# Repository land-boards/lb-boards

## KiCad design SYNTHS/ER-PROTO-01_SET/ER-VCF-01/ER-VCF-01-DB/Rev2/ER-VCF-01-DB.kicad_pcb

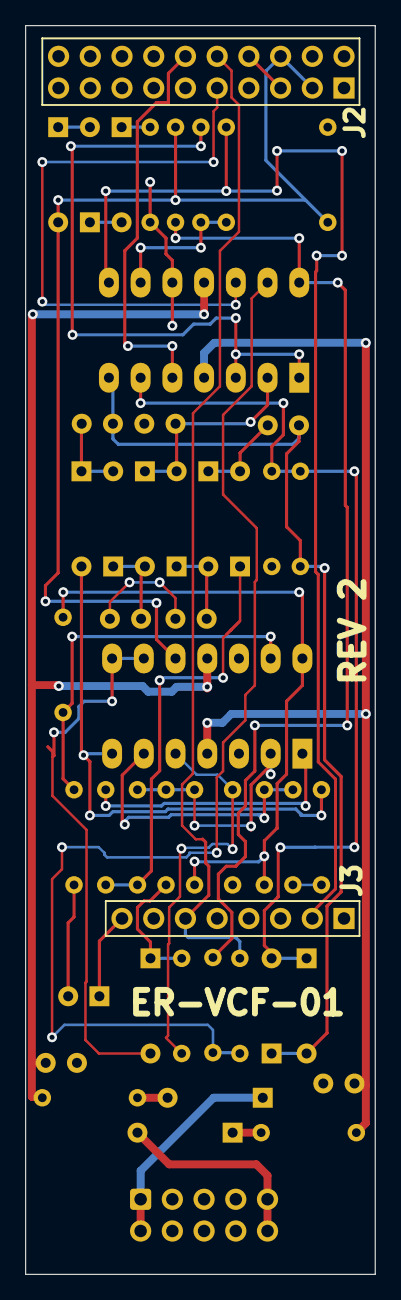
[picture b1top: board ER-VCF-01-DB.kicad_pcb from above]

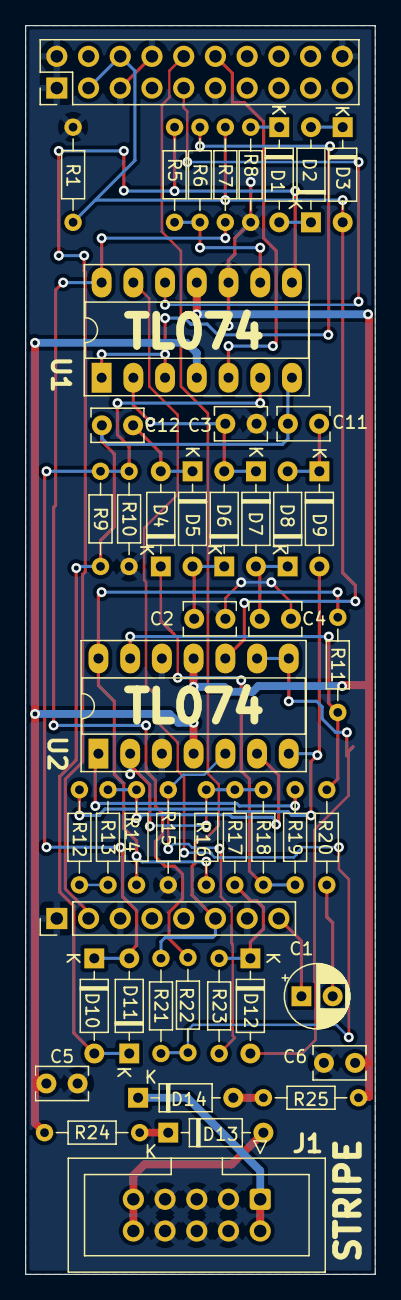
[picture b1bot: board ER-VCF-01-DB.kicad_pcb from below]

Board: 2 copper layers, 28.0 x 100.0 mm, 49 parts (49 on the bottom side), 39 nets.

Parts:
C1: 1uF; CP_Radial_D5.0mm_P2.50mm
C2, C3, C4, C11, C12: 1nF; C_Rect_L4.0mm_W2.5mm_P2.50mm
C5, C6: 0.1uF; C_Rect_L4.0mm_W2.5mm_P2.50mm
D1, D2, D3, D4, D5, D6, D7, D8, D9, D10, D11, D12, D13, D14: 1N4148; D_DO-35_SOD27_P7.62mm_Horizontal
J1: ER-PWR-2X5; IDC-Header_2x05_P2.54mm_Vertical
J2: PROTO01_POTS; PinHeader_2x10_P2.54mm_Vertical
J3: PROTO01_JACKS; PinHeader_1x08_P2.54mm_Vertical
R1, R9: 10K; R_Axial_DIN0204_L3.6mm_D1.6mm_P7.62mm_Horizontal
R5: 47K; R_Axial_DIN0204_L3.6mm_D1.6mm_P7.62mm_Horizontal
R6, R8, R11: 1K; R_Axial_DIN0204_L3.6mm_D1.6mm_P7.62mm_Horizontal
R7, R20, R21, R22: 100K; R_Axial_DIN0204_L3.6mm_D1.6mm_P7.62mm_Horizontal
R10, R12, R19: 2.2K; R_Axial_DIN0204_L3.6mm_D1.6mm_P7.62mm_Horizontal
R13, R14, R15, R16, R17, R18, R23: 33K; R_Axial_DIN0204_L3.6mm_D1.6mm_P7.62mm_Horizontal
R24, R25: 10; R_Axial_DIN0204_L3.6mm_D1.6mm_P7.62mm_Horizontal
U1, U2: TL074; DIP-14_W7.62mm_Socket_LongPads

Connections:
+12V: C5.1, R24.2, U1.4 (V+), U2.4 (V+)
-12V: C6.2, R25.2, U1.11 (V-), U2.11 (V-)
/AUDIO: R11.2, R14.1, R16.1, U2.14
/CV: D12.1 (K), R17.1, R23.1
/J1-T: C1.1, J3.8 (J1-T)
/J3-T: J2.10 (POT2_3_CCW), J3.6 (J3-T), R21.1
/J4-T: J3.2 (J4-T), R5.2, U1.8
/POT2-2: J2.9 (POT2_2_W), U1.12 (+)
/POT4-2: D3.2 (A), J2.3 (POT6_2_W), J2.6 (POT4_2_W), R1.2, R7.2, U2.10 (+)
/POT5-2: J2.12 (POT5_2_W), U1.5 (+)
GND: C2.2, C3.2, C4.2, C5.2, C6.1, J1.3 (GND), J1.4 (GND), J1.5 (GND), J1.6 (GND), J1.7 (GND), J1.8 (GND), J2.1 (GND), J2.2 (POT6_1_CW), J2.5 (POT4_1_CW), J2.8 (POT2_1_CW), J2.11 (POT5_1_CW), J2.20 (GND), J3.1 (J4-S), J3.3 (J2-S), J3.5 (J3-S), J3.7 (J1-S), R1.1, R8.1, R10.1, R15.1, U1.10 (+), U2.3 (+), U2.12 (+)
unnamed: C1.2, R20.1
unnamed: C2.1, D7.2 (A), D8.1 (K)
unnamed: C3.1, D6.2 (A), D7.1 (K), U1.2 (-)
unnamed: C4.1, D5.2 (A), D6.1 (K)
unnamed: C11.1, C12.1, D10.2 (A), D11.1 (K), R9.1, U1.7
unnamed: C11.2, D8.2 (A), D9.1 (K)
unnamed: C12.2, D4.2 (A), D5.1 (K)
unnamed: D1.1 (K), R8.2
unnamed: D1.2 (A), D2.1 (K)
unnamed: D2.2 (A), D3.1 (K)
unnamed: D4.1 (K), R18.2, R19.2
unnamed: D9.2 (A), R12.1, U2.7
unnamed: D10.1 (K), D11.2 (A), R9.2, R10.2, U1.6 (-)
unnamed: D12.2 (A), U2.8, U2.9 (-)
unnamed: D13.1 (K), R24.1
unnamed: D13.2 (A), J1.9 (+12V), J1.10 (+12V)
unnamed: D14.1 (K), J1.1 (-12V), J1.2 (-12V)
unnamed: D14.2 (A), R25.1
unnamed: R5.1, R6.1, U1.9 (-)
unnamed: R6.2, U1.1, U1.3 (+)
unnamed: R11.1, R20.2, U2.13 (-)
unnamed: R12.2, R13.2
unnamed: R13.1, R14.2, U2.6 (-)
unnamed: R15.2, R23.2, U2.5 (+)
unnamed: R16.2, R17.2, R18.1, U2.2 (-)
unnamed: R19.1, U2.1
unnamed: R21.2, R22.1, U1.13 (-)
unnamed: R7.1, R22.2, U1.14

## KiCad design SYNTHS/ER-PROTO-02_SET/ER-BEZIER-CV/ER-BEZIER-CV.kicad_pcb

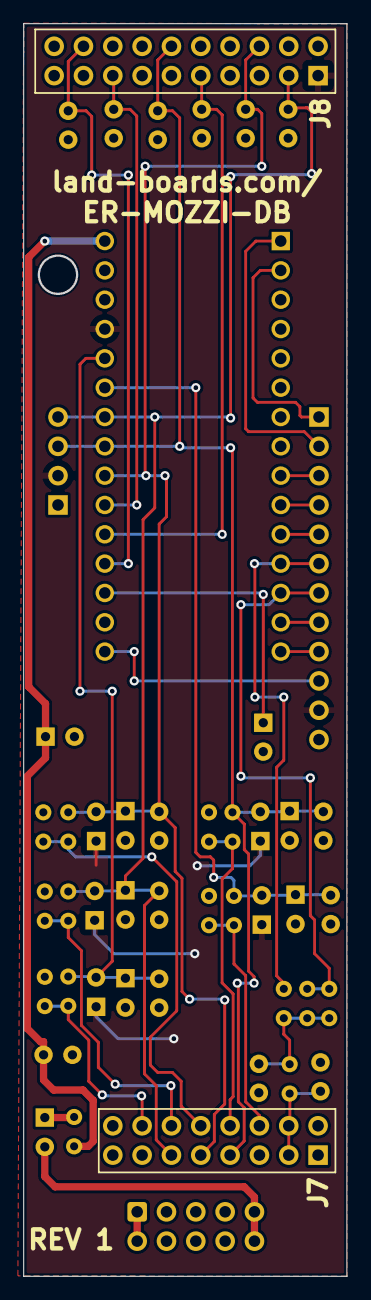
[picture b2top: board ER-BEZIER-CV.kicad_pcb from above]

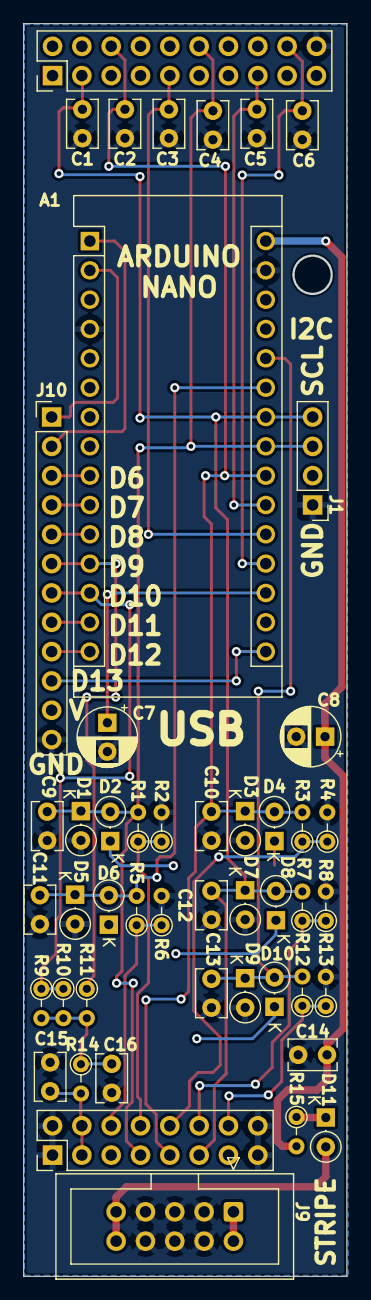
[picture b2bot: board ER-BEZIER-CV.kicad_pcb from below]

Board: 2 copper layers, 28.0 x 108.5 mm, 48 parts (48 on the bottom side), 32 nets.

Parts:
A1: Arduino_Nano_v3.x; Arduino_Nano
C1, C2, C3, C4, C5, C6, C9, C10, C11, C12, C13, C14: 0.1uF; C_Rect_L4.0mm_W2.5mm_P2.50mm
C7: 10uF; CP_Radial_D5.0mm_P2.50mm
C8: 47uF; CP_Radial_D5.0mm_P2.50mm
C15: 10nF; C_Rect_L4.0mm_W2.5mm_P2.50mm
C16: 4.7nF; C_Rect_L4.0mm_W2.5mm_P2.50mm
D1, D2, D3, D4, D5, D6, D7, D8, D9, D10, D11: BAT41; D_DO-35_SOD27_P2.54mm_Vertical_KathodeUp
J1: Conn_01x04; PinHeader_1x04_P2.54mm_Vertical
J7: PROTO02_JACKS; PinHeader_2x08_P2.54mm_Vertical
J8: PROTO01_POTS; PinHeader_2x10_P2.54mm_Vertical
J9: CONN, IDC, 2X5; IDC-Header_2x05_P2.54mm_Vertical
J10: Conn_01x12; PinHeader_1x12_P2.54mm_Vertical
R1, R3, R5, R7, R12: 10K; R_Axial_DIN0204_L3.6mm_D1.6mm_P2.54mm_Vertical
R2, R4, R6, R8, R13: 100K; R_Axial_DIN0204_L3.6mm_D1.6mm_P2.54mm_Vertical
R9, R10: 1M; R_Axial_DIN0204_L3.6mm_D1.6mm_P2.54mm_Vertical
R11, R14: 3.9K; R_Axial_DIN0204_L3.6mm_D1.6mm_P2.54mm_Vertical
R15: 10; R_Axial_DIN0204_L3.6mm_D1.6mm_P2.54mm_Vertical

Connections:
+5V: A1.27 (+5V), D2.1 (K), D4.1 (K), D6.1 (K), D8.1 (K), D10.1 (K), J1.2, J8.1 (GND), J10.11
+12P: A1.30 (VIN), C8.1, C14.1, R15.2
+12V: D11.2 (A), J9.9, J9.10
-12V: J9.1, J9.2
/D0_RX: A1.2 (D0/RX), J10.1
/D1_TX: A1.1 (D1/TX), J10.2
/D6: A1.9 (D6), J10.3
/D7: A1.10 (D7), J10.4
/D8: A1.11 (D8), J10.5
/D9: A1.12 (D9), J10.6, R11.1
/D10: A1.13 (D10), J10.7, R9.1, R10.1
/D11: A1.14 (D11), J10.8
/D12: A1.15 (D12), J10.9
/D13: A1.16 (D13), J10.10
/J1-R_N: A1.22 (A3), C2.1, C10.1, D3.1 (K), D4.2 (A), J7.9 (J1_R_N), J8.6 (POT4_2_W), R3.2
/J1-T: J7.10 (J1_T), R3.1, R4.1
/J2-R_N: A1.23 (A4), C4.1, C9.1, D1.1 (K), D2.2 (A), J1.3, J7.7 (J2_R_N), J8.12 (POT5_2_W), R1.2
/J2-T: J7.8 (J2_T), R1.1, R2.1
/J3-R_N: A1.24 (A5), C1.1, C12.1, D7.1 (K), D8.2 (A), J1.4, J7.11 (J3_R_N), J8.3 (POT6_2_W), R7.2
/J3-T: J7.12 (J3_T), R7.1, R8.1
/J4-T: J7.6 (J4_T), R5.1, R6.1
/J5-T: J7.14 (J5_T), R12.1, R13.1
/J6-R_N: C15.1, J7.3 (J6_R_N), J7.4 (J6_T), R14.2
/POT1-2: A1.19 (A0), C6.1, J8.18 (POT1_2_W)
/POT2-2: A1.20 (A1), C3.1, J8.9 (POT2_2_W)
/POT3-2: A1.21 (A2), C5.1, J8.15 (POT3_2_W)
GND: A1.4 (GND), A1.29 (GND), C1.2, C2.2, C3.2, C4.2, C5.2, C6.2, C7.2, C8.2, C9.2, C10.2, C11.2, C12.2, C13.2, C14.2, C15.2, C16.2, D1.2 (A), D3.2 (A), D5.2 (A), D7.2 (A), D9.2 (A), J1.1, J7.1 (GND), J7.2 (GND), J7.15 (GND), J7.16 (GND), J8.20 (GND), J9.3, J9.4, J9.5, J9.6, J9.7, J9.8, J10.12, R2.2, R4.2, R6.2, R8.2, R13.2
unnamed: A1.18 (AREF), C7.1
unnamed: A1.25 (A6), C11.1, D5.1 (K), D6.2 (A), R5.2
unnamed: A1.26 (A7), C13.1, D9.1 (K), D10.2 (A), R12.2
unnamed: C16.1, R9.2, R10.2, R11.2, R14.1
unnamed: D11.1 (K), R15.1

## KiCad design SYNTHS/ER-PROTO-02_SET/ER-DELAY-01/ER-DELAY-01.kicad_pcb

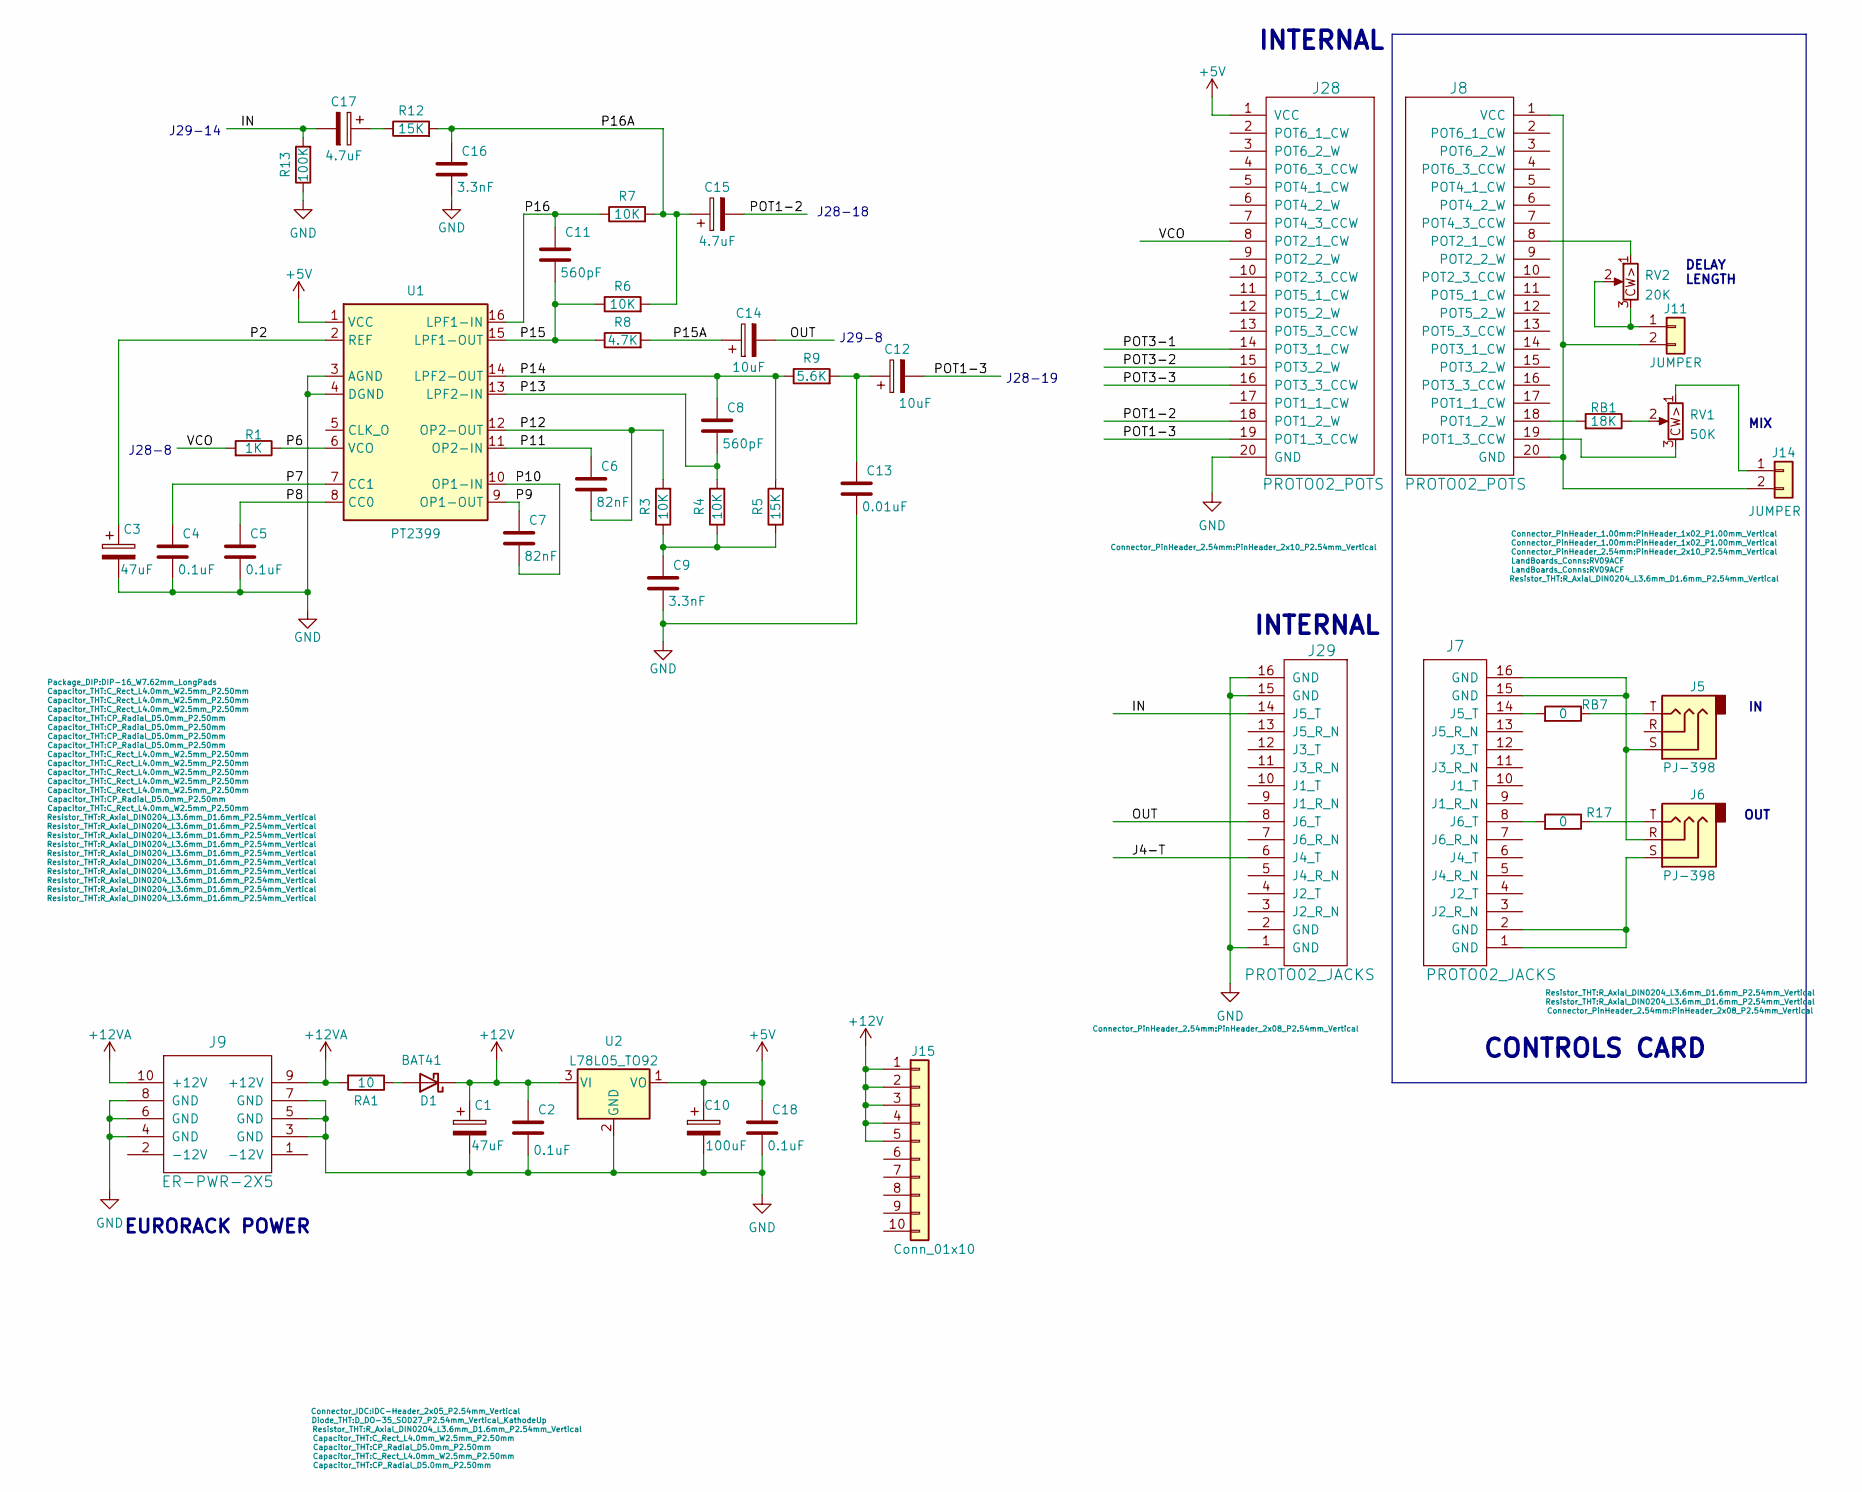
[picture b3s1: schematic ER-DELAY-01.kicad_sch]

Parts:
C1, C3: 47uF; CP_Radial_D5.0mm_P2.50mm
C2, C4, C5, C18: 0.1uF; C_Rect_L4.0mm_W2.5mm_P2.50mm
C6, C7: 82nF; C_Rect_L4.0mm_W2.5mm_P2.50mm
C8, C11: 560pF; C_Rect_L4.0mm_W2.5mm_P2.50mm
C9, C16: 3.3nF; C_Rect_L4.0mm_W2.5mm_P2.50mm
C10: 100uF; CP_Radial_D5.0mm_P2.50mm
C12, C14: 10uF; CP_Radial_D5.0mm_P2.50mm
C13: 0.01uF; C_Rect_L4.0mm_W2.5mm_P2.50mm
C15, C17: 4.7uF; CP_Radial_D5.0mm_P2.50mm
D1: BAT41; D_DO-35_SOD27_P2.54mm_Vertical_KathodeUp
J5, J6: PJ-398; Jack_3.5mm_QingPu_WQP-PJ366ST_Vertical
J7, J29: PROTO02_JACKS; PinHeader_2x08_P2.54mm_Vertical
J8, J28: PROTO02_POTS; PinHeader_2x10_P2.54mm_Vertical
J9: ER-PWR-2X5; IDC-Header_2x05_P2.54mm_Vertical
J11, J14: JUMPER; PinHeader_1x02_P1.00mm_Vertical
J15: Conn_01x10; PinHeader_1x10_P2.54mm_Vertical
R1: 1K; R_Axial_DIN0204_L3.6mm_D1.6mm_P2.54mm_Vertical
R3, R4, R6, R7: 10K; R_Axial_DIN0204_L3.6mm_D1.6mm_P2.54mm_Vertical
R5, R12: 15K; R_Axial_DIN0204_L3.6mm_D1.6mm_P2.54mm_Vertical
R8: 4.7K; R_Axial_DIN0204_L3.6mm_D1.6mm_P2.54mm_Vertical
R9: 5.6K; R_Axial_DIN0204_L3.6mm_D1.6mm_P2.54mm_Vertical
R13: 100K; R_Axial_DIN0204_L3.6mm_D1.6mm_P2.54mm_Vertical
R17: 0; R_Axial_DIN0204_L3.6mm_D1.6mm_P2.54mm_Vertical
RA1: 10; R_Axial_DIN0204_L3.6mm_D1.6mm_P2.54mm_Vertical
RB1: 18K; R_Axial_DIN0204_L3.6mm_D1.6mm_P2.54mm_Vertical
RB7: 0; R_Axial_DIN0204_L3.6mm_D1.6mm_P2.54mm_Vertical
RV1: 50K; RV09ACF
RV2: 20K; RV09ACF
U1: PT2399; DIP-16_W7.62mm_LongPads
U2: L78L05_TO92; TO-92_Inline

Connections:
+5V: C10.1, C18.1, J28.1 (VCC), U1.1 (VCC), U2.1 (VO)
+12V: C1.1, C2.1, D1.1 (K), J15.1, J15.2, J15.3, J15.4, J15.5, U2.3 (VI)
+12VA: J9.9 (+12V), J9.10 (+12V), RA1.2
/IN: C17.2, J29.14 (J5_T), R13.2
/J4-T: J29.6 (J4_T)
/OUT: C14.2, J29.8 (J6_T)
/POT1-2: C15.2, J28.18 (POT1_2_W)
/POT1-3: C12.2, J28.19 (POT1_3_CCW)
/POT3-1: J28.14 (POT3_1_CW)
/POT3-2: J28.15 (POT3_2_W)
/POT3-3: J28.16 (POT3_3_CCW)
/VCO: J28.8 (POT2_1_CW), R1.2
GND: C1.2, C2.2, C3.2, C4.2, C5.2, C9.2, C10.2, C13.2, C16.2, C18.2, J9.3 (GND), J9.4 (GND), J9.5 (GND), J9.6 (GND), J9.7 (GND), J9.8 (GND), J28.20 (GND), J29.1 (GND), J29.15 (GND), J29.16 (GND), R13.1, U1.3 (AGND), U1.4 (DGND), U2.2 (GND)
unnamed: C3.1, U1.2 (REF)
unnamed: C4.1, U1.7 (CC1)
unnamed: C5.1, U1.8 (CC0)
unnamed: C6.1, U1.11 (OP2-IN)
unnamed: C6.2, R3.2, U1.12 (OP2-OUT)
unnamed: C7.1, U1.9 (OP1-OUT)
unnamed: C7.2, U1.10 (OP1-IN)
unnamed: C8.1, R5.2, R9.1, U1.14 (LPF2-OUT)
unnamed: C8.2, R4.2, U1.13 (LPF2-IN)
unnamed: C9.1, R3.1, R4.1, R5.1
unnamed: C11.1, R7.1, U1.16 (LPF1-IN)
unnamed: C11.2, R6.1, R8.1, U1.15 (LPF1-OUT)
unnamed: C12.1, C13.1, R9.2
unnamed: C14.1, R8.2
unnamed: C15.1, C16.1, R6.2, R7.2, R12.2
unnamed: C17.1, R12.1
unnamed: D1.2 (A), RA1.1
unnamed: J5.S, J6.R, J7.15 (GND), J7.16 (GND)
unnamed: J5.T, RB7.1
unnamed: J6.S, J7.1 (GND), J7.2 (GND)
unnamed: J6.T, R17.1
unnamed: J7.8 (J6_T), R17.2
unnamed: J7.14 (J5_T), RB7.2
unnamed: J8.8 (POT2_1_CW), RV2.1
unnamed: J8.18 (POT1_2_W), RB1.2
unnamed: J8.19 (POT1_3_CCW), RV1.3
unnamed: J11.1, RV2.2, RV2.3
unnamed: J8.1 (VCC), J8.20 (GND), J11.2, J14.2
unnamed: J14.1, RV1.1
unnamed: R1.1, U1.6 (VCO)
unnamed: RB1.1, RV1.2

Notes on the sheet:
EURORACK POWER
INTERNAL
CONTROLS CARD
J29-14
MIX
J29-8
J28-18
J28-8
DELAY LENGTH
J28-19
OUT

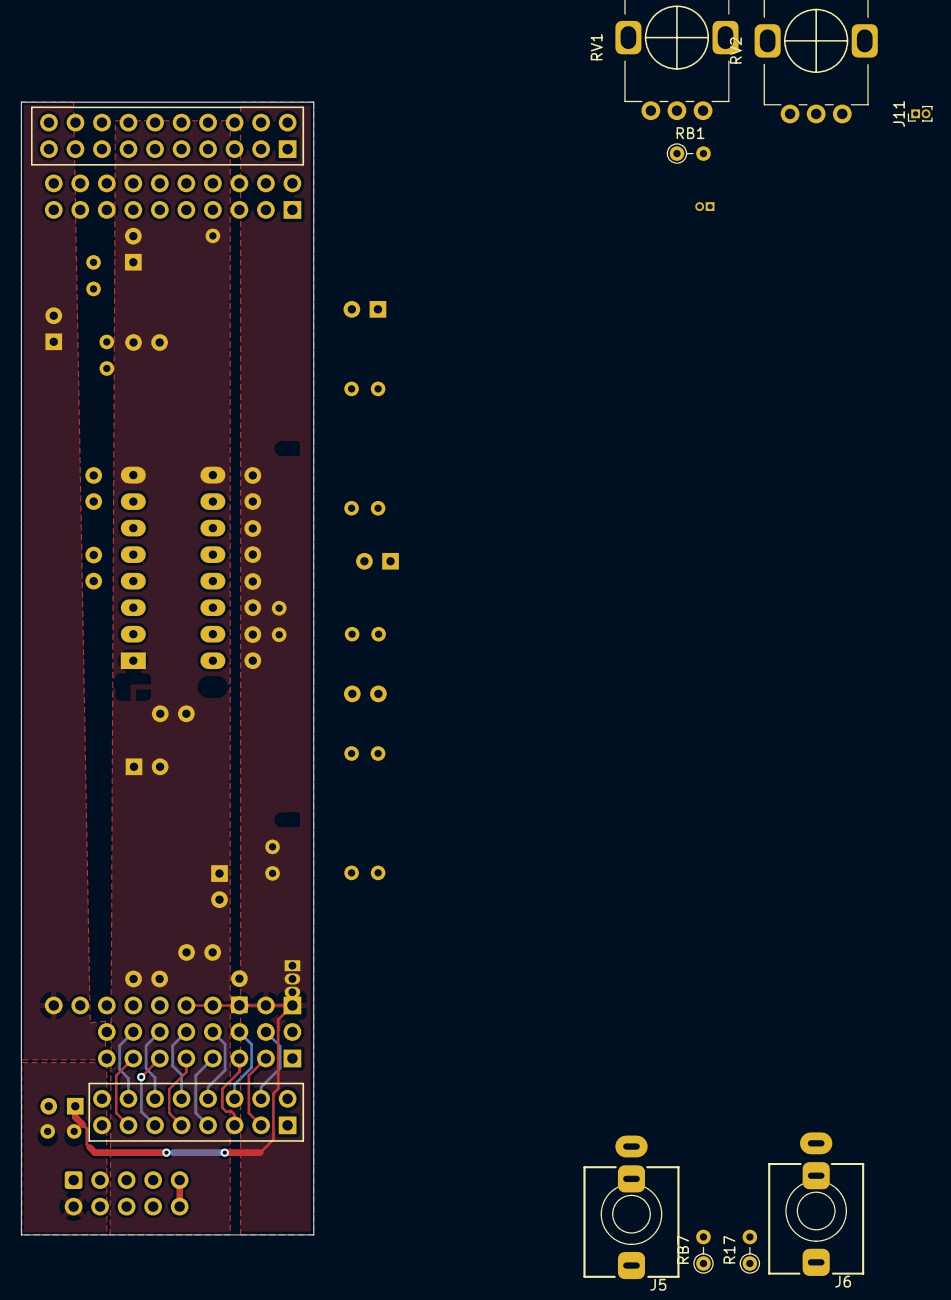
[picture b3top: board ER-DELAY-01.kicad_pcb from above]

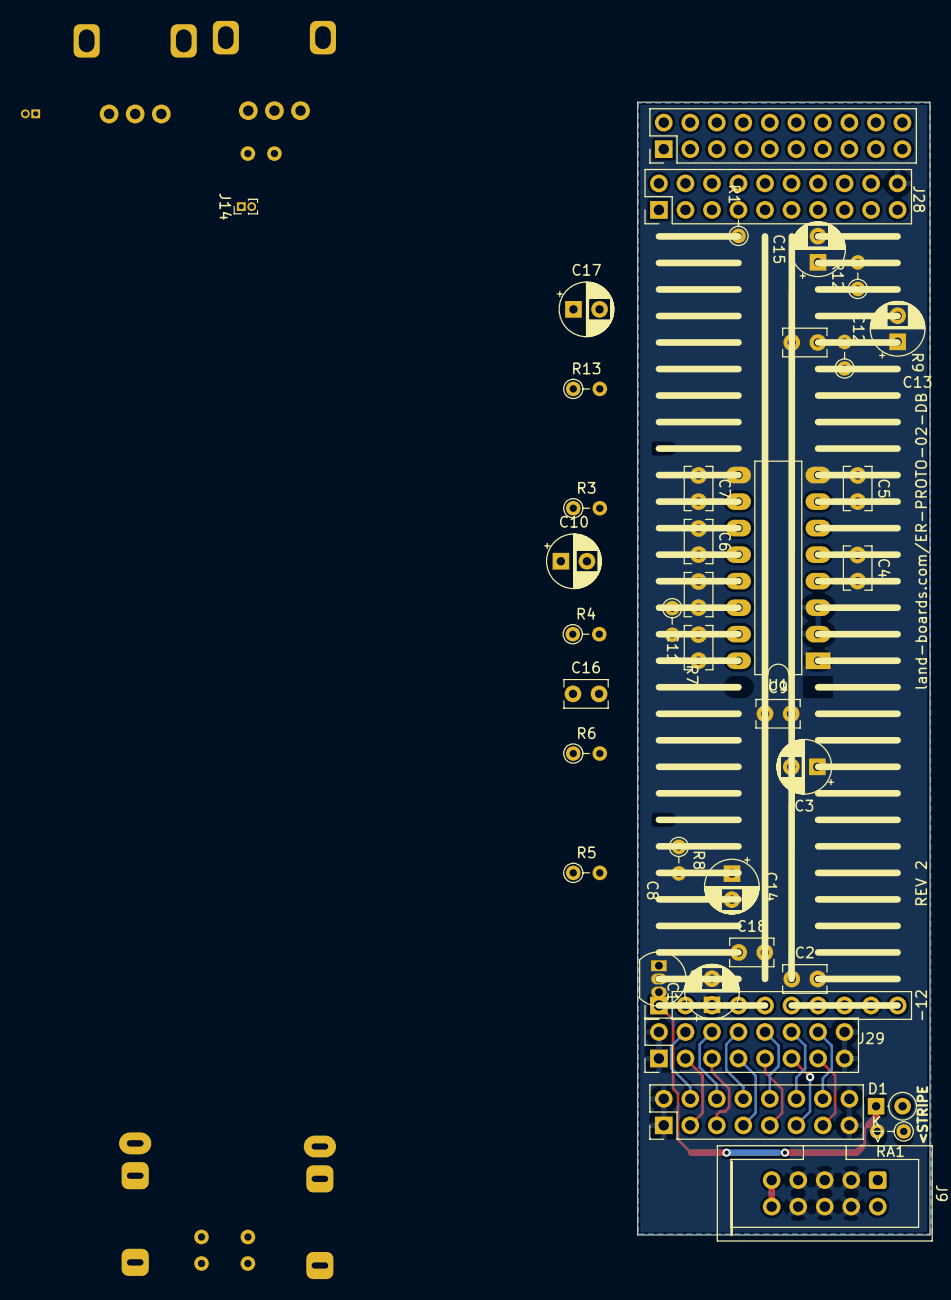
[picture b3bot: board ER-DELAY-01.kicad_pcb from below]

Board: 2 copper layers, 28.0 x 108.5 mm, 47 parts (39 on the bottom side), 40 nets.

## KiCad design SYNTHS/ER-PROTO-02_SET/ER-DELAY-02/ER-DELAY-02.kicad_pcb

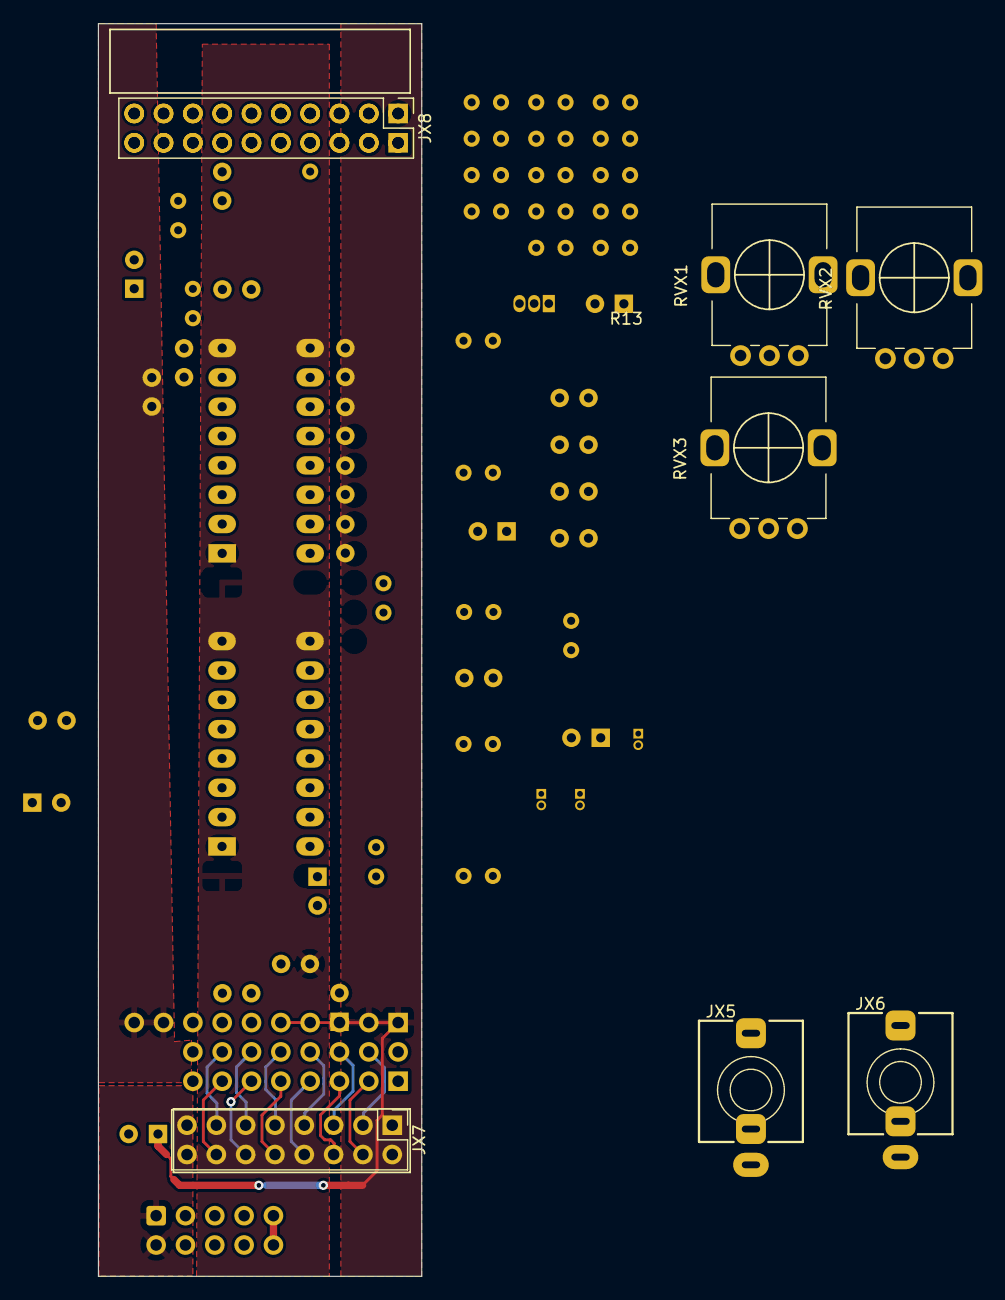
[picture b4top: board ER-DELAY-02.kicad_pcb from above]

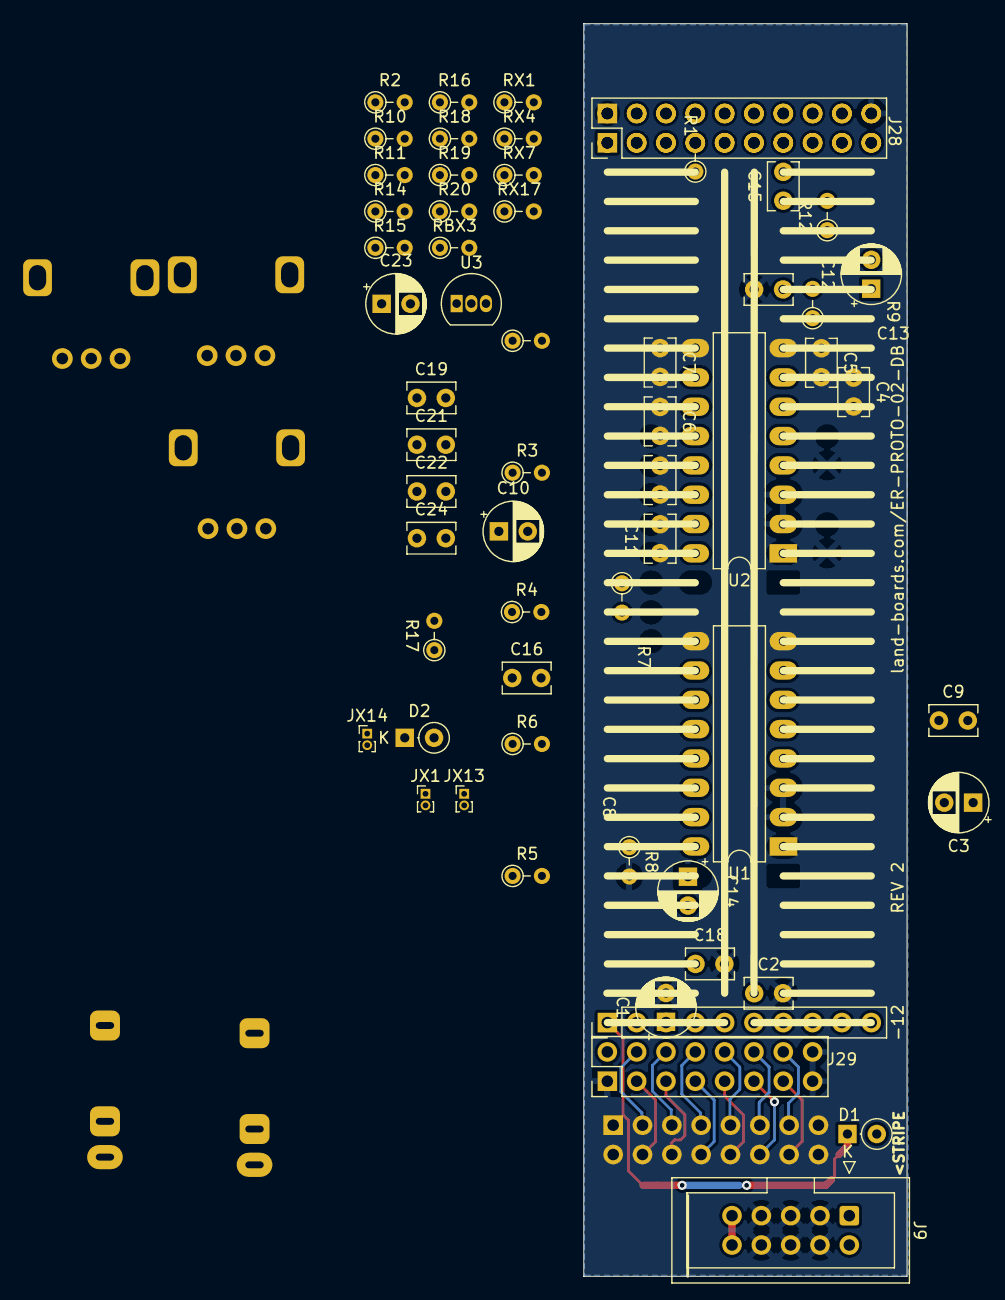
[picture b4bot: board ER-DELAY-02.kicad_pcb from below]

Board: 2 copper layers, 28.0 x 108.5 mm, 66 parts (59 on the bottom side), 55 nets.

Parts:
C1, C14: 47uF; CP_Radial_D5.0mm_P2.50mm
C2, C4, C5, C16, C18: 0.1uF; C_Rect_L4.0mm_W2.5mm_P2.50mm
C3, C23: 1uF; CP_Radial_D5.0mm_P2.50mm
C6, C7: 100nF; C_Rect_L4.0mm_W2.5mm_P2.50mm
C8, C22: 2.2nF; C_Rect_L4.0mm_W2.5mm_P2.50mm
C9: 15nF; C_Rect_L4.0mm_W2.5mm_P2.50mm
C10: 100uF; CP_Radial_D5.0mm_P2.50mm
C11, C13: 2.2uF; C_Rect_L4.0mm_W2.5mm_P2.50mm
C12: 10nF; CP_Radial_D5.0mm_P2.50mm
C15, C19: 47pF; C_Rect_L4.0mm_W2.5mm_P2.50mm
C21: 0.22uF; C_Rect_L4.0mm_W2.5mm_P2.50mm
C24: 4.7nF; C_Rect_L4.0mm_W2.5mm_P2.50mm
D1, D2: BAT41; D_DO-35_SOD27_P2.54mm_Vertical_KathodeUp
J9: ER-PWR-2X5; IDC-Header_2x05_P2.54mm_Vertical
J15: Conn_01x10; PinHeader_1x10_P2.54mm_Vertical
J28: PROTO02_POTS; PinHeader_2x10_P2.54mm_Vertical
J29: PROTO02_JACKS; PinHeader_2x08_P2.54mm_Vertical
JX1, JX13, JX14: JUMPER; PinHeader_1x02_P1.00mm_Vertical
JX5, JX6: PJ-398; Jack_3.5mm_QingPu_WQP-PJ366ST_Vertical
JX7: PROTO02_JACKS; PinHeader_2x08_P2.54mm_Vertical
JX8: PROTO02_POTS; PinHeader_2x10_P2.54mm_Vertical
R1, R2: 10; R_Axial_DIN0204_L3.6mm_D1.6mm_P2.54mm_Vertical
R3, R4, R6, R7, R9, R11, R13, R18: 10K; R_Axial_DIN0204_L3.6mm_D1.6mm_P2.54mm_Vertical
R5, R8: 20K; R_Axial_DIN0204_L3.6mm_D1.6mm_P2.54mm_Vertical
R10, R16: 1M; R_Axial_DIN0204_L3.6mm_D1.6mm_P2.54mm_Vertical
R12, R14, R15, R17, R20: 100K; R_Axial_DIN0204_L3.6mm_D1.6mm_P2.54mm_Vertical
R19: 68K; R_Axial_DIN0204_L3.6mm_D1.6mm_P2.54mm_Vertical
RBX3: 0; R_Axial_DIN0204_L3.6mm_D1.6mm_P2.54mm_Vertical
RVX1: B50K; RV09ACF
RVX2, RVX3: B10K; RV09ACF
RX1, RX17: 1K; R_Axial_DIN0204_L3.6mm_D1.6mm_P2.54mm_Vertical
RX4, RX7: 0; R_Axial_DIN0204_L3.6mm_D1.6mm_P2.54mm_Vertical
U1, U2: PT2399; DIP-16_W7.62mm_LongPads
U3: L78L05_TO92; TO-92_Inline

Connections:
+5V: C10.1, C18.1, J28.1 (VCC), U1.1 (VCC), U2.1 (VCC), U3.1 (VO)
+12V: C1.1, C2.1, D1.1 (K), J15.1, J15.2, J15.3, J15.4, J15.5, U3.3 (VI)
+12VA: J9.9 (+12V), J9.10 (+12V), R1.2
-12V: J15.6, J15.7, J15.8, J15.9, J15.10
-12VA: D2.1 (K), J9.1 (-12V), J9.2 (-12V)
/BUF: J28.10 (POT2_3_CCW), J28.16 (POT3_3_CCW), R12.2
/DRY: C21.2, R17.2, R20.2
/IN: C21.1, J29.14 (J5_T), R16.1
/OUT: C15.2, J29.8 (J6_T), R13.1
/P2: C3.1, U2.2 (REF)
/P7: C4.1, U2.7 (CC1)
/P8: C5.1, U2.8 (CC0)
/P9: C7.1, U2.9 (OP1-OUT)
/P10: C7.2, U2.10 (OP1-IN)
/P11: C6.1, U2.11 (OP2-IN)
/P12: C6.2, R3.2, U2.12 (OP2-OUT)
/P13: C8.2, R4.2, U2.13 (LPF2-IN)
/P14: C8.1, R5.2, R9.1, U2.14 (LPF2-OUT)
/P15: C11.2, R6.1, U2.15 (LPF1-OUT)
/P16: C11.1, R7.1, U2.16 (LPF1-IN)
/REPEAT: J28.9 (POT2_2_W), R14.2
/VCO: J28.18 (POT1_2_W), U2.6 (VCO)
/WET: J28.15 (POT3_2_W), R19.2
GND: C1.2, C2.2, C3.2, C4.2, C5.2, C9.2, C10.2, C13.2, C14.1, C16.2, C18.2, C24.1, J9.3 (GND), J9.4 (GND), J9.5 (GND), J9.6 (GND), J9.7 (GND), J9.8 (GND), J28.20 (GND), J29.1 (GND), J29.15 (GND), J29.16 (GND), R8.2, R10.2, R16.2, U1.3 (AGND), U1.4 (DGND), U2.3 (AGND), U2.4 (DGND), U3.2 (GND)
unnamed: C9.1, R3.1, R4.1, R5.1
unnamed: C12.1, C13.1, R9.2
unnamed: C19.2, R11.1, R15.2
unnamed: C23.1, R18.2
unnamed: C24.2, R6.2, R7.2, R18.1
unnamed: D1.2 (A), R1.1
unnamed: D2.2 (A), R2.1
unnamed: JX1.1, RVX2.1
unnamed: JX1.2, JX8.1 (VCC), JX8.20 (GND), JX13.2, JX14.2
unnamed: JX5.S, JX6.S, JX7.1 (GND), JX7.2 (GND), JX7.15 (GND), JX7.16 (GND)
unnamed: JX5.T, RX7.1
unnamed: JX6.T, RX17.1
unnamed: JX7.14 (J5_T), RX7.2
unnamed: JX7.8 (J6_T), RX17.2
unnamed: JX8.18 (POT1_2_W), RX1.2
unnamed: JX8.19 (POT1_3_CCW), RVX1.3
unnamed: JX8.9 (POT2_2_W), RX4.2
unnamed: JX8.10 (POT2_3_CCW), RVX2.3
unnamed: JX8.15 (POT3_2_W), RBX3.2
unnamed: JX8.16 (POT3_3_CCW), RVX3.3
unnamed: JX13.1, RVX3.1
unnamed: JX14.1, RVX1.1
unnamed: RBX3.1, RVX3.2
unnamed: RVX1.2, RX1.1
unnamed: RVX2.2, RX4.1
unnamed: C19.1, R11.2, R14.1, R17.1
unnamed: C22.2, R15.1
unnamed: C12.2, R10.1
unnamed: R8.1, R12.1
unnamed: C15.1, R13.2, R19.1, R20.1
unnamed: C14.2, C16.1, R2.2

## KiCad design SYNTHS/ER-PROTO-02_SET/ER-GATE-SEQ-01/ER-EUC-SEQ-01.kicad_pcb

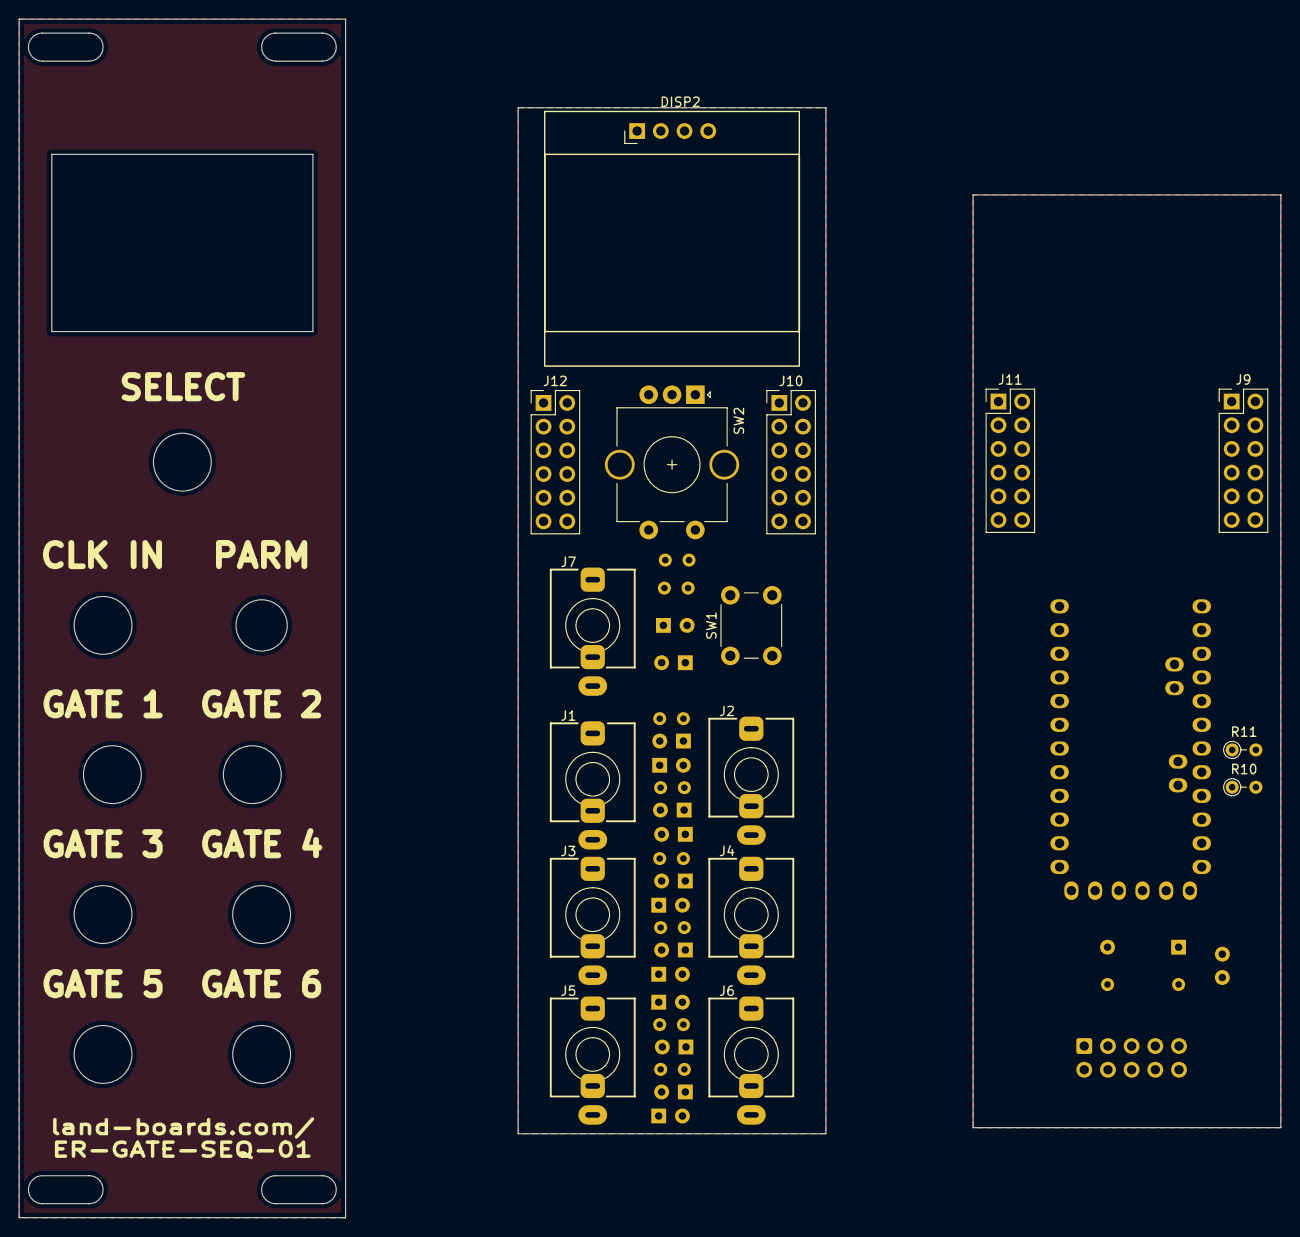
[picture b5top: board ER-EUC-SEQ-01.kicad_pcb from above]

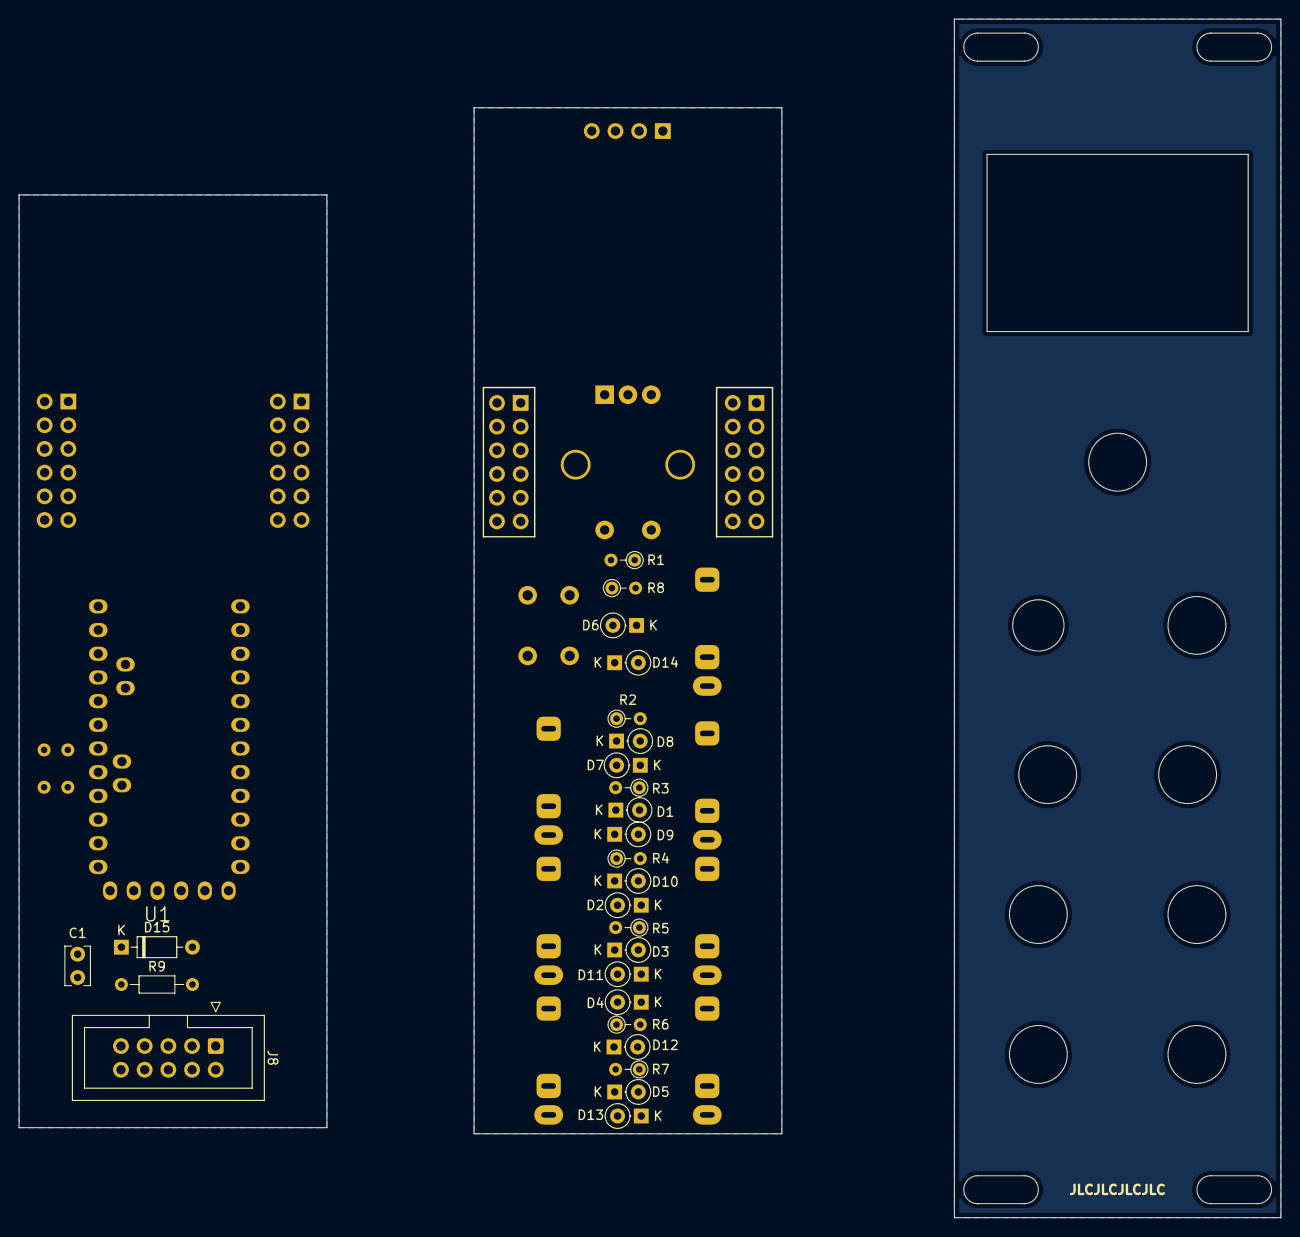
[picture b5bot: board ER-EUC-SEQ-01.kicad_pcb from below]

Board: 2 copper layers, 135.3 x 128.5 mm, 43 parts (27 on the bottom side), 25 nets, no tracks yet.

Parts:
C1: 0.1uF; C_Rect_L4.0mm_W2.5mm_P2.50mm
D1, D2, D3, D4, D5, D6, D7, D8, D9, D10, D11, D12, D13, D14: BAT41; D_DO-35_SOD27_P2.54mm_Vertical_KathodeUp
D15: BAT41; D_DO-35_SOD27_P7.62mm_Horizontal
DISP2: I2C_OLED_128X64; OLED-128X64
J1, J2, J3, J4, J5, J6, J7: PJ398SM; Jack_3.5mm_QingPu_WQP-PJ366ST_Vertical
J8: ER-PWR-2X5; IDC-Header_2x05_P2.54mm_Vertical
J9, J10, J11, J12: HDR, 2x6; PinHeader_2x06_P2.54mm_Vertical
R1: 100K; R_Axial_DIN0204_L3.6mm_D1.6mm_P2.54mm_Vertical
R2, R3, R4, R5, R6, R7, R8: 470; R_Axial_DIN0204_L3.6mm_D1.6mm_P2.54mm_Vertical
R9: 10; R_Axial_DIN0204_L3.6mm_D1.6mm_P7.62mm_Horizontal
R10, R11: 2.2K; R_Axial_DIN0204_L3.6mm_D1.6mm_P2.54mm_Vertical
SW1: SW_Push; SW_PUSH_6mm_H13mm
SW2: RotaryEncoder_Switch; RotaryEncoder_Alps_EC11E-Switch_Vertical_H20mm_CircularMoun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
U1: ARDUPROMINI-ArduProMiniTKB; ArduProMini

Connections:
+5V: D1.1 (K), D2.1 (K), D3.1 (K), D4.1 (K), D5.1 (K), D6.1 (K), D7.1 (K), J9.1, J9.2, J10.1, J10.2, J11.1, J11.2, J12.1, J12.2, R10.2, R11.2, U1.22 (Vcc2)
+12V: C1.2, D15.1 (K), U1.19 (RAW)
/G1: J1.T, R2.2
/G2: J2.T, R3.2
/G3: J3.T, R4.2
/G4: J4.T, R5.2
/G5: J5.T, R6.2
/G6: J6.T, R7.2
/GATE1: D7.2 (A), D8.1 (K), J11.8, J12.8, R2.1, U1.14 (D5)
/GATE2: D1.2 (A), D9.1 (K), J9.3, J10.3, R3.1, U1.15 (D6)
/GATE3: D2.2 (A), D10.1 (K), J11.9, J12.9, R4.1, U1.16 (D7)
/GATE4: D3.2 (A), D11.1 (K), J9.5, J10.5, R5.1, U1.17 (D8)
/GATE5: D4.2 (A), D12.1 (K), J11.10, J12.10, R6.1, U1.18 (D9)
/GATE6: D5.2 (A), D13.1 (K), J9.7, J10.7, R7.1, U1.30 (D10)
/GATE_IN: D6.2 (A), D14.1 (K), J11.7, J12.7, R1.2, R8.1, U1.27 (D13)
/IN: J7.T, R8.2
/PB: J9.9, J10.9, SW1.2, U1.28 (D12)
/PB2: J9.10, J10.10, SW2.S1, U1.29 (D11)
/ROTA: J11.5, J12.5, SW2.A, U1.11 (D2)
/ROTB: J11.6, J12.6, SW2.B, U1.12 (D3)
/SCL: DISP2.3 (SCK), J11.3, J12.3, R10.1, U1.31 (A5/SCL)
/SDA: DISP2.4 (SDA), J11.4, J12.4, R11.1, U1.32 (A4/SDA)
GND: C1.1, D8.2 (A), D9.2 (A), D10.2 (A), D11.2 (A), D12.2 (A), D13.2 (A), D14.2 (A), J1.S, J2.S, J3.S, J4.S, J5.S, J6.S, J7.S, J8.3 (GND), J8.4 (GND), J8.5 (GND), J8.6 (GND), J8.7 (GND), J8.8 (GND), J9.11, J9.12, J10.11, J10.12, J11.11, J11.12, J12.11, J12.12, R1.1, SW1.1, SW2.C, SW2.S2, U1.10 (GND), U1.20 (GND3)
unnamed: D15.2 (A), R9.2
unnamed: J8.9 (+12V), J8.10 (+12V), R9.1
